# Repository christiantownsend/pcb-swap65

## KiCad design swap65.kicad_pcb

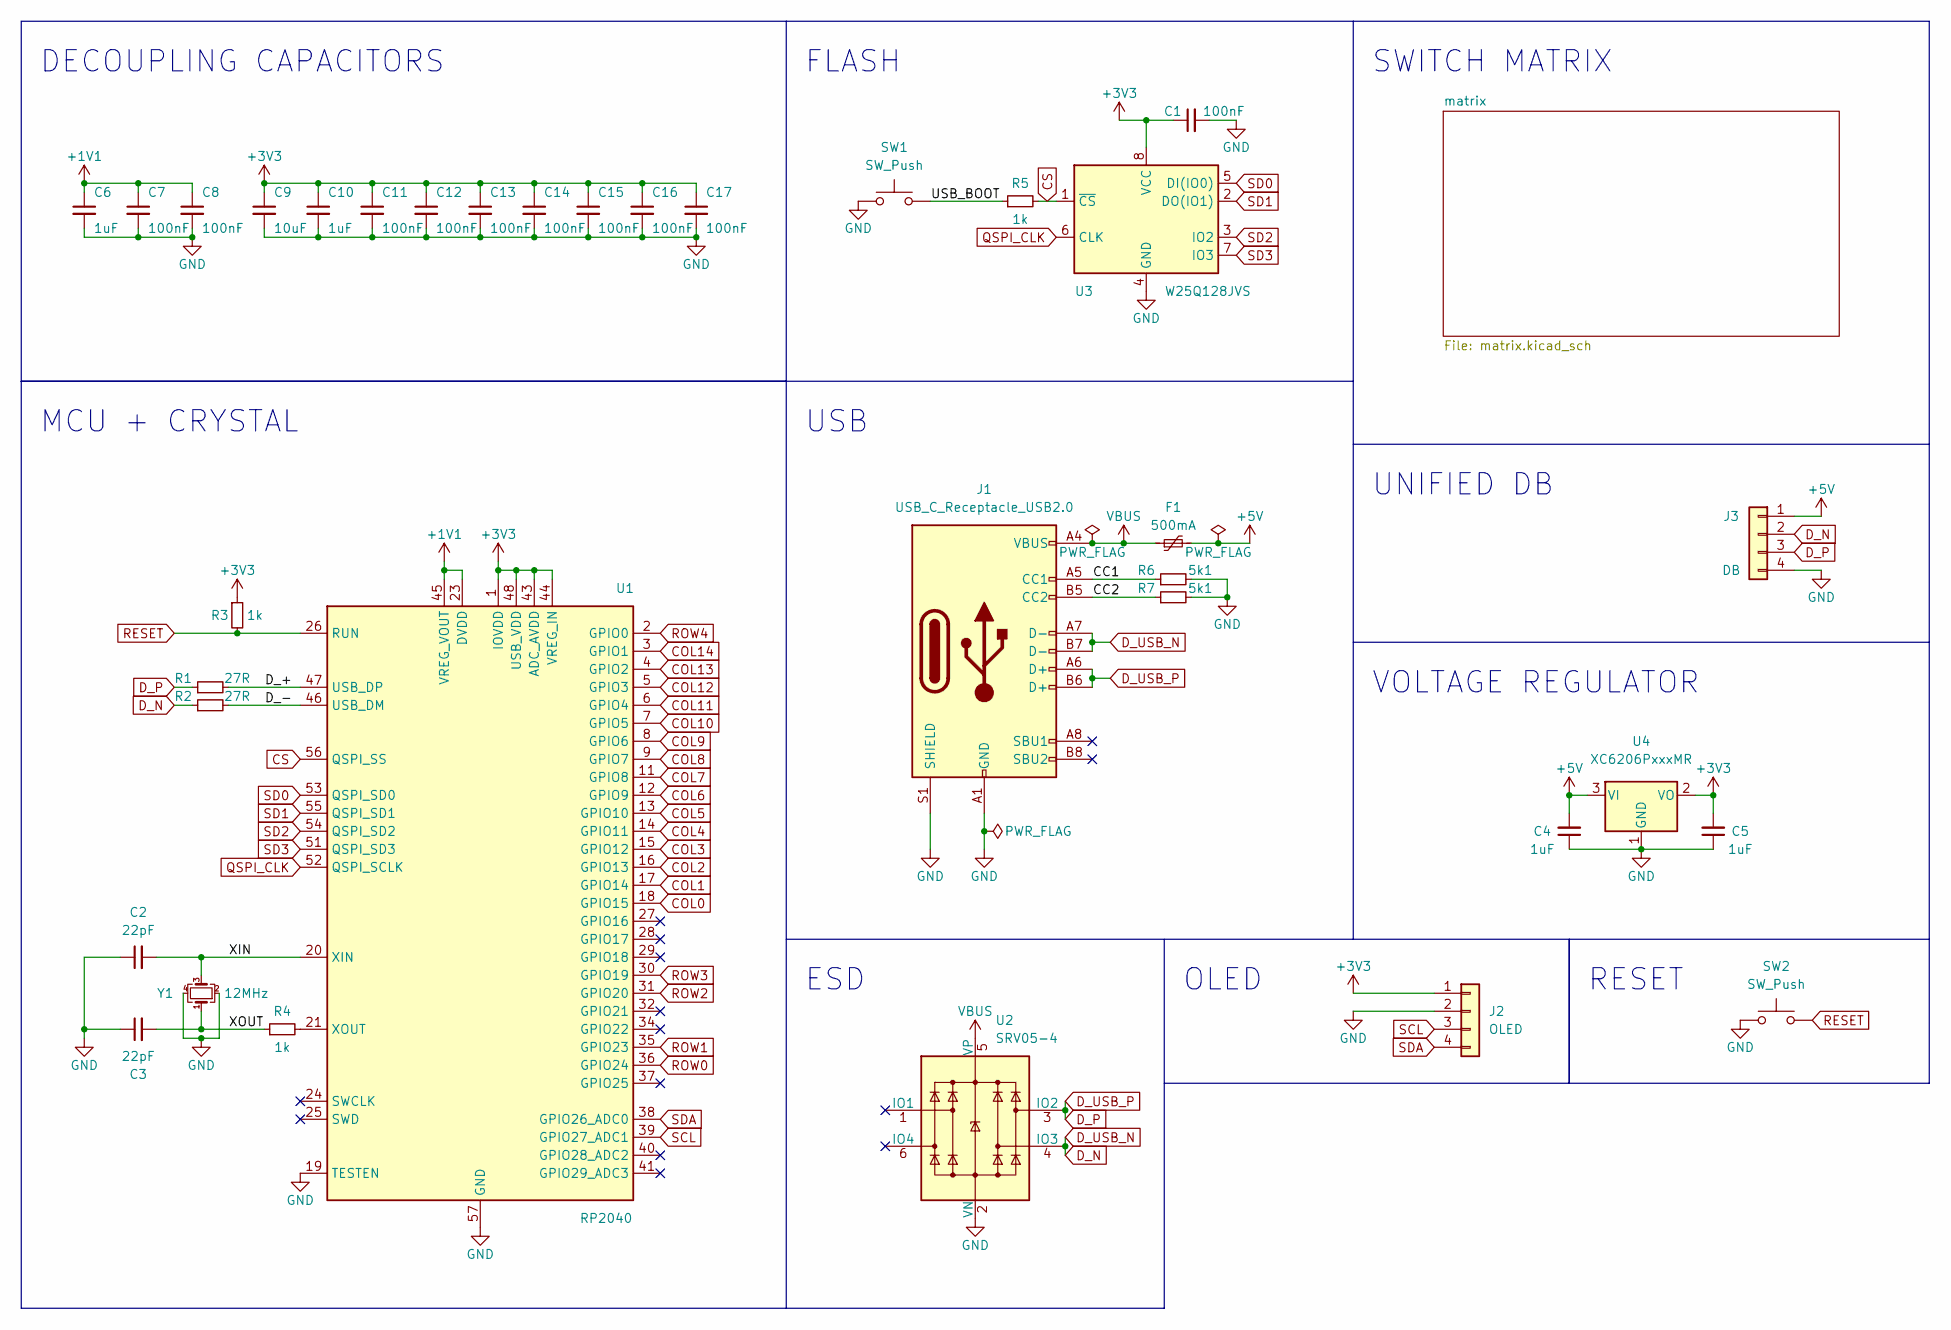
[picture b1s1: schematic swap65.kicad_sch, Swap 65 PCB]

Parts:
C1, C7, C8, C11, C12, C13, C14, C15, C16, C17: 100nF; C_0402_1005Metric_Pad0.74x0.62mm_HandSolder
C2, C3: 22pF; C_0402_1005Metric_Pad0.74x0.62mm_HandSolder
C4, C5, C6, C10: 1uF; C_0402_1005Metric_Pad0.74x0.62mm_HandSolder
C9: 10uF; C_0402_1005Metric_Pad0.74x0.62mm_HandSolder
F1: 500mA; Fuse_0805_2012Metric_Pad1.15x1.40mm_HandSolder
J1: USB_C_Receptacle_USB2.0; USB_C_Receptacle_HRO_TYPE-C-31-M-12
J2: OLED; PinHeader_1x04_P2.54mm_Vertical
J3: DB; JST_SH_SM04B-SRSS-TB_1x04-1MP_P1.00mm_Horizontal
R1, R2: 27R; R_0402_1005Metric_Pad0.72x0.64mm_HandSolder
R3, R4, R5: 1k; R_0402_1005Metric_Pad0.72x0.64mm_HandSolder
R6, R7: 5k1; R_0402_1005Metric_Pad0.72x0.64mm_HandSolder
SW1, SW2: SW_Push; SW_SPST_SKQG_WithStem
U1: RP2040; QFN-56-1EP_7x7mm_P0.4mm_EP3.2x3.2mm
U2: SRV05-4; SOT-23-6-routable
U3: W25Q128JVS; SOIC-8_5.23x5.23mm_P1.27mm
U4: XC6206PxxxMR; SOT-23-3
Y1: 12MHz; Crystal_SMD_2016-4Pin_2.0x1.6mm

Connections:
+1V1: C6.1, C7.1, C8.1, U1.23 (DVDD), U1.45 (VREG_VOUT), U1.50 (DVDD)
+3V3: C1.1, C5.2, C9.1, C10.1, C11.1, C12.1, C13.1, C14.1, C15.1, C16.1, C17.1, J2.1, R3.1, U1.1 (IOVDD), U1.10 (IOVDD), U1.22 (IOVDD), U1.33 (IOVDD), U1.42 (IOVDD), U1.43 (ADC_AVDD), U1.44 (VREG_IN), U1.48 (USB_VDD), U1.49 (IOVDD), U3.8 (VCC), U4.2 (VO)
+5V: C4.2, F1.2, J3.1, U4.3 (VI)
/CC1: J1.A5 (CC1), R6.1
/CC2: J1.B5 (CC2), R7.1
/D_+: R1.2, U1.47 (USB_DP)
/D_-: R2.2, U1.46 (USB_DM)
/USB_BOOT: R5.1, SW1.2
/XIN: C2.2, U1.20 (XIN), Y1.3
/XOUT: C3.2, R4.1, Y1.1
COL0: U1.18 (GPIO15); also elsewhere on the board
COL1: U1.17 (GPIO14); also elsewhere on the board
COL2: U1.16 (GPIO13); also elsewhere on the board
COL3: U1.15 (GPIO12); also elsewhere on the board
COL4: U1.14 (GPIO11); also elsewhere on the board
COL5: U1.13 (GPIO10); also elsewhere on the board
COL6: U1.12 (GPIO9); also elsewhere on the board
COL7: U1.11 (GPIO8); also elsewhere on the board
COL8: U1.9 (GPIO7); also elsewhere on the board
COL9: U1.8 (GPIO6); also elsewhere on the board
COL10: U1.7 (GPIO5); also elsewhere on the board
COL11: U1.6 (GPIO4); also elsewhere on the board
COL12: U1.5 (GPIO3); also elsewhere on the board
COL13: U1.4 (GPIO2); also elsewhere on the board
COL14: U1.3 (GPIO1); also elsewhere on the board
CS: R5.2, U1.56 (QSPI_SS), U3.1 (~CS)
D_N: J1.A7 (D-), J1.B7 (D-), J3.2, R2.1, U2.4 (IO3)
D_P: J1.A6 (D+), J1.B6 (D+), J3.3, R1.1, U2.3 (IO2)
GND: C1.2, C2.1, C3.1, C4.1, C5.1, C6.2, C7.2, C8.2, C9.2, C10.2, C11.2, C12.2, C13.2, C14.2, C15.2, C16.2, C17.2, J1.A1 (GND), J1.A12 (GND), J1.B1 (GND), J1.B12 (GND), J1.S1 (SHIELD), J2.2, J3.4, R6.2, R7.2, SW1.1, SW2.1, U1.19 (TESTEN), U1.57 (GND), U2.2 (VN), U3.4 (GND), U4.1 (GND), Y1.2, Y1.4
unnamed: R4.2, U1.21 (XOUT)
QSPI_CLK: U1.52 (QSPI_SCLK), U3.6 (CLK)
RESET: R3.2, SW2.2, U1.26 (RUN)
ROW0: U1.36 (GPIO24); also elsewhere on the board
ROW1: U1.35 (GPIO23); also elsewhere on the board
ROW2: U1.31 (GPIO20); also elsewhere on the board
ROW3: U1.30 (GPIO19); also elsewhere on the board
ROW4: U1.2 (GPIO0); also elsewhere on the board
SCL: J2.3, U1.39 (GPIO27_ADC1)
SD0: U1.53 (QSPI_SD0), U3.5 (DI(IO0))
SD1: U1.55 (QSPI_SD1), U3.2 (DO(IO1))
SD2: U1.54 (QSPI_SD2), U3.3 (IO2)
SD3: U1.51 (QSPI_SD3), U3.7 (IO3)
SDA: J2.4, U1.38 (GPIO26_ADC0)
VBUS: F1.1, J1.A4 (VBUS), J1.A9 (VBUS), J1.B4 (VBUS), J1.B9 (VBUS), U2.5 (VP)

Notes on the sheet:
RESET
OLED
UNIFIED DB
VOLTAGE REGULATOR
ESD
DECOUPLING CAPACITORS
SWITCH MATRIX
FLASH
MCU + CRYSTAL
USB

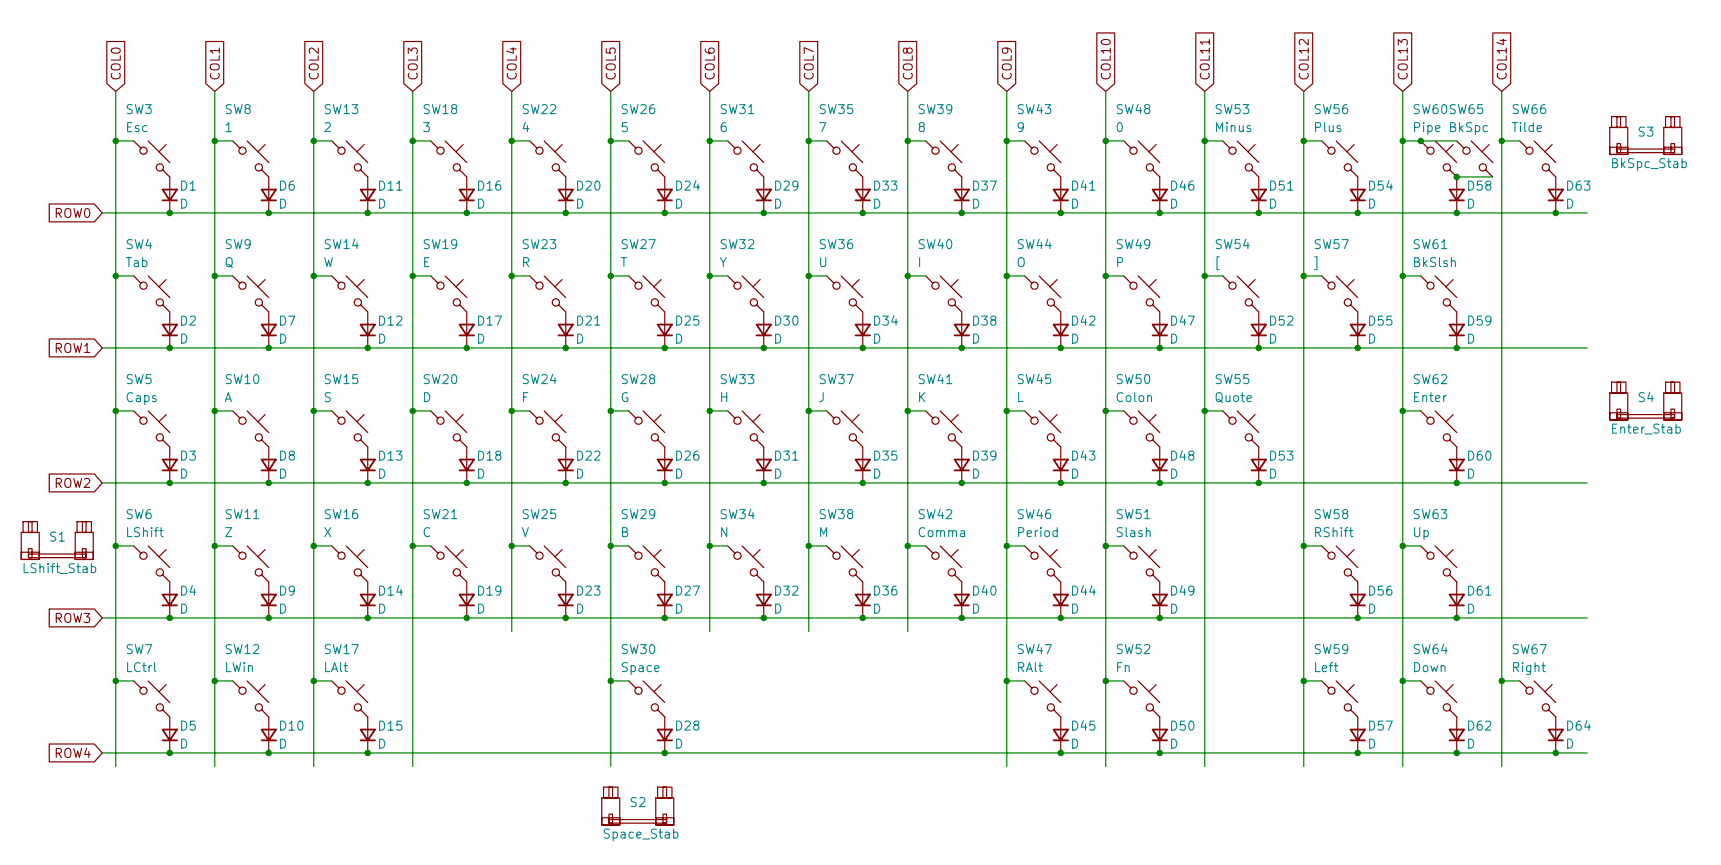
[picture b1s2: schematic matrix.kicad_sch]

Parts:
D1, D2, D3, D4, D5, D6, D7, D8, D9, D10, D11, D12, D13, D14, D15, D16, D17, D18, D19, D20, D21, D22, D23, D24, D25, D26, D27, D28, D29, D30, D31, D32, D33, D34, D35, D36, D37, D38, D39, D40, D41, D42, D43, D44, D45, D46, D47, D48, D49, D50, D51, D52, D53, D54, D55, D56, D57, D58, D59, D60, D61, D62, D63, D64: D; D_0805_2012Metric_Pad1.15x1.40mm_HandSolder
S1: LShift_Stab; STAB_MX_P_2.25u
S2: Space_Stab; STAB_MX_P_6.25u
S3: BkSpc_Stab; STAB_MX_P_2u
S4: Enter_Stab; STAB_MX_P_2.25u
SW3: Esc; SW_MX_HS_1u
SW4: Tab; SW_MX_HS_1.5u
SW5: Caps; SW_MX_HS_1.75u
SW6: LShift; SW_MX_HS_1u
SW7: LCtrl; SW_MX_HS_1.25u
SW8: 1; SW_MX_HS_1u
SW9: Q; SW_MX_HS_1u
SW10: A; SW_MX_HS_1u
SW11: Z; SW_MX_HS_1u
SW12: LWin; SW_MX_HS_1.25u
SW13: 2; SW_MX_HS_1u
SW14: W; SW_MX_HS_1u
SW15: S; SW_MX_HS_1u
SW16: X; SW_MX_HS_1u
SW17: LAlt; SW_MX_HS_1.25u
SW18: 3; SW_MX_HS_1u
SW19: E; SW_MX_HS_1u
SW20: D; SW_MX_HS_1u
SW21: C; SW_MX_HS_1u
SW22: 4; SW_MX_HS_1u
SW23: R; SW_MX_HS_1u
SW24: F; SW_MX_HS_1u
SW25: V; SW_MX_HS_1u
SW26: 5; SW_MX_HS_1u
SW27: T; SW_MX_HS_1u
SW28: G; SW_MX_HS_1u
SW29: B; SW_MX_HS_1u
SW30: Space; SW_MX_HS_1u
SW31: 6; SW_MX_HS_1u
SW32: Y; SW_MX_HS_1u
SW33: H; SW_MX_HS_1u
SW34: N; SW_MX_HS_1u
SW35: 7; SW_MX_HS_1u
SW36: U; SW_MX_HS_1u
SW37: J; SW_MX_HS_1u
SW38: M; SW_MX_HS_1u
SW39: 8; SW_MX_HS_1u
SW40: I; SW_MX_HS_1u
SW41: K; SW_MX_HS_1u
SW42: Comma; SW_MX_HS_1u
SW43: 9; SW_MX_HS_1u
SW44: O; SW_MX_HS_1u
SW45: L; SW_MX_HS_1u
SW46: Period; SW_MX_HS_1u
SW47: RAlt; SW_MX_HS_1.25u
SW48: 0; SW_MX_HS_1u
SW49: P; SW_MX_HS_1u
SW50: Colon; SW_MX_HS_1u
SW51: Slash; SW_MX_HS_1u
SW52: Fn; SW_MX_HS_1.25u
SW53: Minus; SW_MX_HS_1u
SW54: [; SW_MX_HS_1u
SW55: Quote; SW_MX_HS_1u
SW56: Plus; SW_MX_HS_1u
SW57: ]; SW_MX_HS_1u
SW58: RShift; SW_MX_HS_1.75u
SW59: Left; SW_MX_HS_1u
SW60: Pipe; SW_MX_HS_S_1u
SW61: BkSlsh; SW_MX_HS_1.5u
SW62: Enter; SW_MX_HS_1u
SW63: Up; SW_MX_HS_1u
SW64: Down; SW_MX_HS_1u
SW65: BkSpc; SW_MX_HS_S_1u
SW66: Tilde; SW_MX_HS_S_1u
SW67: Right; SW_MX_HS_1u

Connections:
COL0: SW3.1, SW4.1, SW5.1, SW6.1, SW7.1; also elsewhere on the board
COL1: SW8.1, SW9.1, SW10.1, SW11.1, SW12.1; also elsewhere on the board
COL2: SW13.1, SW14.1, SW15.1, SW16.1, SW17.1; also elsewhere on the board
COL3: SW18.1, SW19.1, SW20.1, SW21.1; also elsewhere on the board
COL4: SW22.1, SW23.1, SW24.1, SW25.1; also elsewhere on the board
COL5: SW26.1, SW27.1, SW28.1, SW29.1, SW30.1; also elsewhere on the board
COL6: SW31.1, SW32.1, SW33.1, SW34.1; also elsewhere on the board
COL7: SW35.1, SW36.1, SW37.1, SW38.1; also elsewhere on the board
COL8: SW39.1, SW40.1, SW41.1, SW42.1; also elsewhere on the board
COL9: SW43.1, SW44.1, SW45.1, SW46.1, SW47.1; also elsewhere on the board
COL10: SW48.1, SW49.1, SW50.1, SW51.1, SW52.1; also elsewhere on the board
COL11: SW53.1, SW54.1, SW55.1; also elsewhere on the board
COL12: SW56.1, SW57.1, SW58.1, SW59.1; also elsewhere on the board
COL13: SW60.1, SW61.1, SW62.1, SW63.1, SW64.1, SW65.1; also elsewhere on the board
COL14: SW66.1, SW67.1; also elsewhere on the board
unnamed: D1.2 (A), SW3.2
unnamed: D2.2 (A), SW4.2
unnamed: D3.2 (A), SW5.2
unnamed: D4.2 (A), SW6.2
unnamed: D5.2 (A), SW7.2
unnamed: D6.2 (A), SW8.2
unnamed: D7.2 (A), SW9.2
unnamed: D8.2 (A), SW10.2
unnamed: D9.2 (A), SW11.2
unnamed: D10.2 (A), SW12.2
unnamed: D11.2 (A), SW13.2
unnamed: D12.2 (A), SW14.2
unnamed: D13.2 (A), SW15.2
unnamed: D14.2 (A), SW16.2
unnamed: D15.2 (A), SW17.2
unnamed: D16.2 (A), SW18.2
unnamed: D17.2 (A), SW19.2
unnamed: D18.2 (A), SW20.2
unnamed: D19.2 (A), SW21.2
unnamed: D20.2 (A), SW22.2
unnamed: D21.2 (A), SW23.2
unnamed: D22.2 (A), SW24.2
unnamed: D23.2 (A), SW25.2
unnamed: D24.2 (A), SW26.2
unnamed: D25.2 (A), SW27.2
unnamed: D26.2 (A), SW28.2
unnamed: D27.2 (A), SW29.2
unnamed: D28.2 (A), SW30.2
unnamed: D29.2 (A), SW31.2
unnamed: D30.2 (A), SW32.2
unnamed: D31.2 (A), SW33.2
unnamed: D32.2 (A), SW34.2
unnamed: D33.2 (A), SW35.2
unnamed: D34.2 (A), SW36.2
unnamed: D35.2 (A), SW37.2
unnamed: D36.2 (A), SW38.2
unnamed: D37.2 (A), SW39.2
unnamed: D38.2 (A), SW40.2
unnamed: D39.2 (A), SW41.2
unnamed: D40.2 (A), SW42.2
unnamed: D41.2 (A), SW43.2
unnamed: D42.2 (A), SW44.2
unnamed: D43.2 (A), SW45.2
unnamed: D44.2 (A), SW46.2
unnamed: D45.2 (A), SW47.2
unnamed: D46.2 (A), SW48.2
unnamed: D47.2 (A), SW49.2
unnamed: D48.2 (A), SW50.2
unnamed: D49.2 (A), SW51.2
unnamed: D50.2 (A), SW52.2
unnamed: D51.2 (A), SW53.2
unnamed: D52.2 (A), SW54.2
unnamed: D53.2 (A), SW55.2
unnamed: D54.2 (A), SW56.2
unnamed: D55.2 (A), SW57.2
unnamed: D56.2 (A), SW58.2
unnamed: D57.2 (A), SW59.2
unnamed: D58.2 (A), SW60.2, SW65.2
unnamed: D59.2 (A), SW61.2
unnamed: D60.2 (A), SW62.2
unnamed: D61.2 (A), SW63.2
unnamed: D62.2 (A), SW64.2
unnamed: D63.2 (A), SW66.2
unnamed: D64.2 (A), SW67.2
ROW0: D1.1 (K), D6.1 (K), D11.1 (K), D16.1 (K), D20.1 (K), D24.1 (K), D29.1 (K), D33.1 (K), D37.1 (K), D41.1 (K), D46.1 (K), D51.1 (K), D54.1 (K), D58.1 (K), D63.1 (K); also elsewhere on the board
ROW1: D2.1 (K), D7.1 (K), D12.1 (K), D17.1 (K), D21.1 (K), D25.1 (K), D30.1 (K), D34.1 (K), D38.1 (K), D42.1 (K), D47.1 (K), D52.1 (K), D55.1 (K), D59.1 (K); also elsewhere on the board
ROW2: D3.1 (K), D8.1 (K), D13.1 (K), D18.1 (K), D22.1 (K), D26.1 (K), D31.1 (K), D35.1 (K), D39.1 (K), D43.1 (K), D48.1 (K), D53.1 (K), D60.1 (K); also elsewhere on the board
ROW3: D4.1 (K), D9.1 (K), D14.1 (K), D19.1 (K), D23.1 (K), D27.1 (K), D32.1 (K), D36.1 (K), D40.1 (K), D44.1 (K), D49.1 (K), D56.1 (K), D61.1 (K); also elsewhere on the board
ROW4: D5.1 (K), D10.1 (K), D15.1 (K), D28.1 (K), D45.1 (K), D50.1 (K), D57.1 (K), D62.1 (K), D64.1 (K); also elsewhere on the board

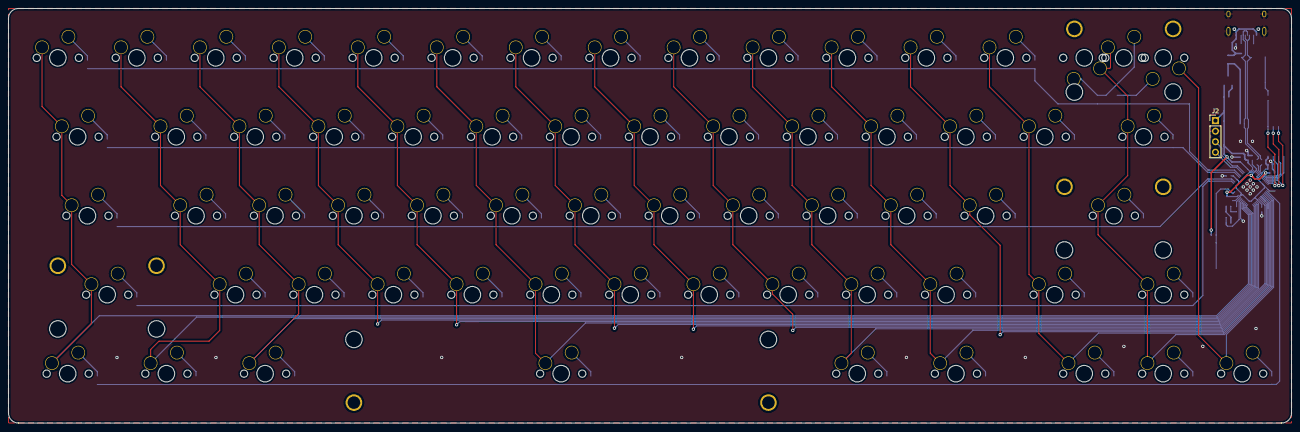
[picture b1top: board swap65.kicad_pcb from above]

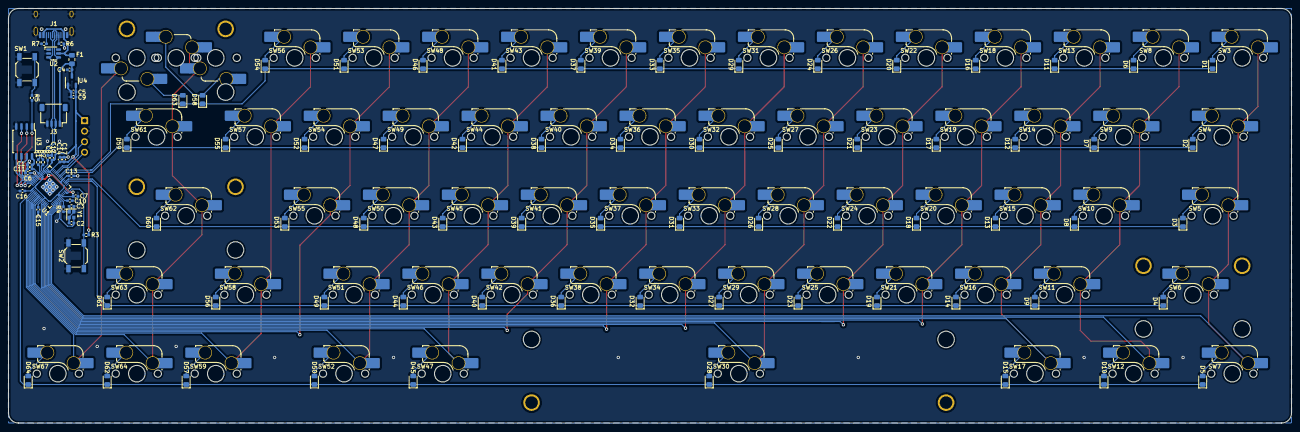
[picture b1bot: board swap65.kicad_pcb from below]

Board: 2 copper layers, 309.6 x 100.0 mm, 168 parts (167 on the bottom side), 108 nets.

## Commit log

2022-12-27 add gitignore
2022-12-27 initialize kicad project
2022-12-27 add marbastlib
2022-12-27 add autosave dir to gitignore
2022-12-27 switch marbastlib to untested branch
2022-12-27 add marbastlib to kicad project
2022-12-28 wired up first pass of schematic
2022-12-29 did initial routing of MCU and USB
2022-12-30 routed columns
2022-12-30 completed first pass at routing
2022-12-31 added screen header to schematic
2022-12-31 completed route pass 1
2022-12-31 organized schematic
2022-12-31 swapped USD to basic part and added db jst connector
2022-12-31 routed usb and jst connector
2022-12-31 routed mcu
2022-12-31 second pass at routing complete
2022-12-31 fixed courtyard overlap
2023-01-01 finalized second pass at routing
